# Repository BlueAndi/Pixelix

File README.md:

# PIXELIX <!-- omit in toc -->

Full RGB LED matrix, based on an ESP32 and WS2812B LEDs.

Click on the preview to see the video.

\

___

## Table of Content <!-- omit in toc -->

- [Motivation](#motivation)
- [Introduction](#introduction)
- [Features](#features)
- [Original Setup](#original-setup)
- [Attention](#attention)
- [Supported Development Boards](#supported-development-boards)
  - [Recommendation](#recommendation)
  - [Special Variants](#special-variants)
- [Installation](#installation)
  - [Install A Prebuilt Release With The Web USB Installer](#install-a-prebuilt-release-with-the-web-usb-installer)
  - [Install A Prebuilt Release Manually](#install-a-prebuilt-release-manually)
  - [Build And Install The Software Yourself](#build-and-install-the-software-yourself)
  - [Verify The Installation](#verify-the-installation)
  - [Update A Running PIXELIX](#update-a-running-pixelix)
- [Very First Startup](#very-first-startup)
  - [Variant 1: Configure WiFi station SSID and passphrase using a browser](#variant-1-configure-wifi-station-ssid-and-passphrase-using-a-browser)
  - [Variant 2: Configure WiFi station SSID and passphrase using a serial terminal](#variant-2-configure-wifi-station-ssid-and-passphrase-using-a-serial-terminal)
  - [PIXELIX Is Ready](#pixelix-is-ready)
- [User Interface](#user-interface)
  - [One button control](#one-button-control)
  - [Two button control (LILYGO® T-Display ESP32-S3)](#two-button-control-lilygo-t-display-esp32-s3)
  - [Three button control (Ulanzi TC001)](#three-button-control-ulanzi-tc001)
  - [Remote button](#remote-button)
- [Details](#details)
- [FAQ](#faq)
  - [Where to change panel topology of the LED matrix?](#where-to-change-panel-topology-of-the-led-matrix)
  - [How to change text properties?](#how-to-change-text-properties)
  - [The display only shows an error code, like "E4". What does that mean?](#the-display-only-shows-an-error-code-like-e4-what-does-that-mean)
  - [How can I use animated icons?](#how-can-i-use-animated-icons)
  - [How do I know that my sensor is recognized?](#how-do-i-know-that-my-sensor-is-recognized)
  - [Why do I see sometimes values from the LDR in the SensorPlugin, although no LDR is installed?](#why-do-i-see-sometimes-values-from-the-ldr-in-the-sensorplugin-although-no-ldr-is-installed)
  - [How can I use alternative icons?](#how-can-i-use-alternative-icons)
  - [Is it possible to use a font with 8px height?](#is-it-possible-to-use-a-font-with-8px-height)
  - [How to configure the date/time format?](#how-to-configure-the-datetime-format)
  - [How to configure my own list of plugins?](#how-to-configure-my-own-list-of-plugins)
  - [Is there an easy way to rotate the display by 180° ? I need to turn the display when putting it into a housing](#is-there-an-easy-way-to-rotate-the-display-by-180--i-need-to-turn-the-display-when-putting-it-into-a-housing)
- [Used Libraries](#used-libraries)
- [Issues, Ideas And Bugs](#issues-ideas-and-bugs)
- [License](#license)
- [Contribution](#contribution)

## Motivation

My initial goal was to have a remote display that would show multiple kind of information and run reliably 24/7. Can be connected to the local network via WiFi and controlled via REST API or Websocket. PIXELIX was born!

## Introduction

PIXELIX firmware runs on ESP32 boards and controls RGB LED matrices or TFT displays. It can display the time, date, weather, text, animations, and more.
It requires no cloud connection or smart home system, but its REST and MQTT APIs integrate with [Home Assistant](https://www.home-assistant.io/) and other smart home systems.

## Features

- Supports 32x8, 32x16 and 64x64 LED matrix size out of the box.
- Supports some small TFT displays to simulate a LED matrix in retro style.
- Display static or scrolling text, as well as static or animated icons (BMP, GIF and additional for boards with PSRAM PNG and WEBP).
- Includes a web interface for configuration and control.
- Supports REST and MQTT API for remote control and integration with other systems, like [Home Assistant](https://www.home-assistant.io/).
- Extendable with custom effects and animations by plugins. See list of [plugins](./doc/PLUGINS.md).
- Its plugin concept allows to scale for different development boards.

Not every feature is available on every development board. For example, MQTT generally requires a board with at least 8 MB of flash, except for the Ulanzi TC001. See the `config<variant>.ini` files in the [config](./config) folder for details.

| Some impressions                                                           |                                                                |
| -------------------------------------------------------------------------- | -------------------------------------------------------------- |
|                 |    |
|  |  |
|        | ...                                                            |

The native environment runs PIXELIX as an application on Windows and Linux without requiring hardware. It displays a simulated LED grid in a window and serves its web interface on local port 8080. Melodies that would play through a board's buzzer use the host's audio device. You can mute them with the _Mute_ entry in the simulator window's menu bar.

## Original Setup

The original setup for development and the first release was:

- [ESP32 DevKitV1](https://github.com/playelek/pinout-doit-32devkitv1)
- WS2812B 5050 8x32 RGB Flexible LED Matrix Panel
- Power supply 5 V / 4 A

The following diagram shows the minimum wiring setup, for example, for the ESP32 DevKit V1. Wiring may differ depending on your development board.

## Attention

> :warning: **If you power the development board and LED matrix via USB**, be careful: excessive LED current can damage the ESP32 board. Avoid increasing the display brightness or filling it completely with white pixels. Use an external power supply rated for at least 5 V / 4 A.

> :information_source: To protect your hardware and your eyes, PIXELIX starts at a low brightness. The maximum current is also limited by software.

## Supported Development Boards

In the meantime several other boards are supported as well. You can find them in the [list of boards](./doc/boards/README.md).
If your board is not listed in the main branch, please have a look in the [Development branch](https://github.com/BlueAndi/Pixelix/tree/Development) too.

With the [Ulanzi TC001 smart pixel clock](https://www.ulanzi.com/products/ulanzi-pixel-smart-clock-2882) you even don't need to assemble the electronic and mechanic together.

### Recommendation

If you assemble your own Pixelix hardware, its recommended to use a development board with the following properties:

- 8 MB flash or more. 4 MB flash modules are still supported, but the functionality is limited.
- A esp32 dual core variant, which provides more processing power.
- PSRAM for image formats that require more memory than the available internal RAM, depending on the enabled features.

### Special Variants

Additional supported variants, which were original not in focus:

- [LILYGO&reg; TTGO T-Display ESP32 WiFi and Bluetooth Module Development Board For Arduino 1.14 Inch LCD](http://www.lilygo.cn/prod_view.aspx?TypeId=50033&Id=1126&FId=t3:50033:3)
- [LILYGO&reg; T-Display ESP32-S3 1.9 inch ST7789 LCD Display Touch Screen Development Board](https://www.lilygo.cc/products/t-display-s3)
- Limited HUB75 panel support, configured for the ESP32-DoIt DevKit v1 and the Adafruit MatrixPortal S3 development board.

Although PIXELIX was designed to show information, that is pushed or pulled via REST API, the following sensors can be directly connected and evaluated:

- Temperature and humidity sensors DHTx
- Temperature and humidity sensors SHT3x
- Digitial microphone INMP441 for some sound reactive stuff.

## Installation

PIXELIX can be installed in two different ways. Decide first which one applies to you, because it determines whether you need a build toolchain at all.

| Your situation                                                                                                                                                                                                                 | Way to go                                                                                                                                                                                                                                    |
| ------------------------------------------------------------------------------------------------------------------------------------------------------------------------------------------------------------------------------ | -------------------------------------------------------------------------------------------------------------------------------------------------------------------------------------------------------------------------------------------- |
| You use one of the [supported development boards](#supported-development-boards) with its standard display and the panel wiring matches.                                                                                       | Install a prebuilt release. No toolchain required, nothing needs to be compiled. Use the [web USB installer](#install-a-prebuilt-release-with-the-web-usb-installer) or [flash the binaries manually](#install-a-prebuilt-release-manually). |
| Your board/display combination is not released, your LED matrix size or panel topology is different, you want another set of plugins, you want to rotate the display by 180&deg; or you want to develop a plugin or fix a bug. | [Build and install the software yourself](#build-and-install-the-software-yourself).                                                                                                                                                         |

Every release provides ready-to-flash binaries for all supported board and display combinations. They are named after their build environment, e.g. ```esp32doit-devkit-v1-LED-32x8```, which encodes the development board as well as the display type and its resolution.

> :warning: A prebuilt binary has the LED matrix width/height, the panel topology and the list of plugins compiled in. None of them can be changed later in the web interface. If one of them does not match your hardware, you have to build the software yourself.

### Install A Prebuilt Release With The Web USB Installer

This is the easiest way and the recommended one for everybody who does not want to touch the source code. The installer runs completely in the browser, writes a full flash image (bootloader, partition table, factory image, firmware and filesystem) and can hand over the WiFi credentials over USB afterwards.

1. Open the [PIXELIX USB installer](https://blueandi.github.io/Pixelix/) in a Chromium based desktop browser, like Chrome, Edge, Opera or Brave. It is based on the Web Serial API, which is not available in Firefox, Safari or on mobile devices.
2. Choose the version. The latest stable release is preselected. All releases from version 11 on are offered; pre-releases are marked as such and are not recommended for productive use.
3. Choose your board and display configuration.
4. Connect the development board to your PC with a data capable USB cable and select the serial device once.
5. Start _Erase and install_. Note, that the flash is erased completely, which includes all settings of a previous installation.
    - To keep the settings of a previous installation, enable _Keep settings_ before. The flash is then not erased and the device settings stored in NVS survive: WiFi credentials, hostname, web login, brightness, timezone and so on. The slot configuration, MQTT, sensor calibration, timers and the plugin configuration are reset in any case, because they are part of the filesystem which is always written. Don't use it for the first installation on a board.
6. Keep the USB cable connected and continue with the WiFi setup on the same page. If that succeeds, you can skip the [Very First Startup](#very-first-startup).

If the board does not enter the download mode automatically, follow the BOOT/RESET sequence shown on the page. This is typically necessary for the ESP32 DevKit V1.

### Install A Prebuilt Release Manually

Use this way if no Chromium based browser is available or if you prefer the classic Espressif tools.

1. Download the binaries from the [latest release](https://github.com/BlueAndi/Pixelix/releases).
2. Write them to the flash with the Espressif Flash Download Tool (Windows only) or with esptool (any OS). The detailed steps, the required flash addresses and the flash layout are documented in [Upload/Update the software and the filesystem](./doc/config/SW-UPDATE.md).
3. Continue with the [Very First Startup](#very-first-startup).

See the [software update guide](./doc/config/SW-UPDATE.md#native-application) for native release downloads and installation.

### Build And Install The Software Yourself

> :information_source: The order matters. Configure the display **before** the first build, because the display configuration is compiled into the firmware.

1. Setup the [toolchain](./doc/config/TOOLCHAIN-INSTALLATION.md).
2. Configure your display in ```./config/display.ini```:
   - Adapt _CONFIG_LED_MATRIX_WIDTH_ and _CONFIG_LED_MATRIX_HEIGHT_ according to your LED matrix.
   - Change _CONFIG_LED_TOPO_ according to your physical panel topology. Take a look how your pixels are wired on the pcb and use the following page to choose the right one: [https://github.com/Makuna/NeoPixelBus/wiki/Layout-objects](https://github.com/Makuna/NeoPixelBus/wiki/Layout-objects)
   - Optional: set _CONFIG_DISPLAY_ROTATE180_ to 1 to [rotate the display by 180&deg;](#is-there-an-easy-way-to-rotate-the-display-by-180--i-need-to-turn-the-display-when-putting-it-into-a-housing).
3. Optional: adapt the [list of plugins](#how-to-configure-my-own-list-of-plugins) in the corresponding ```./config/config*.ini```.
4. [Build the software](./doc/config/SW-BUILD.md) and check whether the toolchain works.
5. [Upload the software and the filesystem](./doc/config/SW-UPDATE.md) to the target. Note, that both parts are necessary, the firmware and the filesystem image.
6. Continue with the [Very First Startup](#very-first-startup).

### Verify The Installation

Independent of the way you installed PIXELIX, verify that the LED panel topology is correct and that you see the "Hello World" on the display. If the text is mirrored, scrambled or spread over the wrong rows, the panel topology does not match and the software has to be built with the right _CONFIG_LED_TOPO_ setting.

### Update A Running PIXELIX

Once PIXELIX runs and its web interface is accessible, the firmware and the filesystem can be updated over WiFi with the PIXELIX Updater: [https://github.com/BlueAndi/PixelixUpdater](https://github.com/BlueAndi/PixelixUpdater). You can access the Updater through the submenu "Update" of PIXELIX's web interface. Reinstalling via USB is not necessary for an update.

## Very First Startup

When the device starts for the very first time, the WiFi station SSID and passphrase settings are empty. They can be configured in two possible ways:

1. Using the browser and set them in the captive portal.
2. Using a serial terminal connecting via USB.

### Variant 1: Configure WiFi station SSID and passphrase using a browser

As long as no WiFi station SSID and passphrase are configured, PIXELIX spawns a WiFi access point automatically on every startup. Just wait until it shows the SSID of the access point, search for it with your mobile device and connect.

Once the WiFi station SSID and passphrase are configured, PIXELIX connects to your WiFi network instead. To get back into the access point mode on purpose - e.g. after you replaced your router - restart the device and **keep the button pressed** until the access point SSID is shown.

- SSID: **pixelix-&lt;DEVICE-ID&gt;**
- Passphrase: **Luke, I am your father.**

Depending on your device, you may see a notification prompting you to open the captive portal. Otherwise, enter `http://192.169.4.1` in your browser's address bar.

Use the following default credentials to get access to the PIXELIX web interface:

- User: **luke**
- Password: **skywalker**

### Variant 2: Configure WiFi station SSID and passphrase using a serial terminal

Connect PIXELIX to your PC via USB and start a serial terminal. Use the following commands to set the WiFi SSID and passphrase of your home WiFi network:

- Write WiFi passphrase: ```write wifi passphrase <your-passphrase>```
- Write WiFi SSID: ```write wifi ssid <your-ssid>```
- Restart PIXELIX: ```restart```
- Get IP-address: ```get ip```
- Get hostname: ```get hostname```
- Get status: ```get status```
  - A status of 0 means everything is ok.
  - For any other status, see the [low-level error code table](#the-display-only-shows-a-error-code-like-e4-what-does-that-mean). For example, status 1 corresponds to error code E1.

Use ```help``` to get a list of all supported commands.

### PIXELIX Is Ready

After configuration, restart PIXELIX. It will then be available on your Wi-Fi network.

To change what is displayed, open the web interface and use the same credentials as for the captive portal in Variant 1. On the **Display** page, configure it to suit your needs.

## User Interface

Pixelix can be controlled with buttons. Most of the development boards are supported with just one user button.

### One button control

- 1 short pulse: Activates the next slot.
- 2 short pulses: Activates the previous slot.
- 3 short pulses: Activates next fade effect.
- 4 short pulses: IP address is shown.
- 5 short pulses: Toggle display power on/off.
- Long pressed: Increases the display brightness until maximum and then decreases until minimum. After that it will again increases it and so on.

### Two button control (LILYGO&reg; T-Display ESP32-S3)

- Left button:
  - 1 short pulses: Activates the previous slot.
  - 2 short pulses: Toggle display power on/off.
  - Long pressed: Decreases the display brightness until minimum.
- Right button
  - 1 short pulse: Activates the next slot.
  - 2 short pulses: Activates next fade effect.
  - 3 short pulses: IP address is shown.
  - Long pressed: Increases the display brightness until maximum.

### Three button control (Ulanzi TC001)

- Left button:
  - 1 short pulses: Activates the previous slot.
  - Long pressed: Decreases the display brightness until minimum.
- Ok button:
  - 1 short pulses: Activates next fade effect.
  - 2 short pulses: IP address is shown.
  - Long pressed: Toggle display power on/off.
- Right button
  - 1 short pulse: Activates the next slot.
  - Long pressed: Increases the display brightness until maximum.

### Remote button

If the display's location is hard to reach, the remote user button feature can be used. It is controllable via REST API and perfect for remote buttons like the [Shelly Button 1](https://shelly.cloud/products/shelly-button-1-smart-home-automation-device/).

## Details

- [Home Assistant](./doc/HOMEASSISTANT.md)
- [REST API](https://app.swaggerhub.com/apis/BlueAndi/Pixelix/1.10.0)
- [MQTT API](./doc/MQTT.md)
- More information is in the [documentation](./doc/README.md) folder.

## FAQ

### Where to change panel topology of the LED matrix?

Adapt in ```./config/display.ini``` the _CONFIG_LED_MATRIX_WIDTH_ and _CONFIG_LED_MATRIX_HEIGHT_ according your LED matrix and change _CONFIG_LED_TOPO_ according to your physical panel topology. Take a look how your pixels are wired on the pcb and use the following page to choose the right one: [https://github.com/Makuna/NeoPixelBus/wiki/Layout-objects](https://github.com/Makuna/NeoPixelBus/wiki/Layout-objects)

### How to change text properties?

Text properties can be changed using different keywords added to the string to be displayed.
In order to be able to use these keywords, they must be inside curly braces, otherwise they will only be treated as text.

The following keywords are available:

| Keyword                               | Description                                                                              |
| ------------------------------------- | ---------------------------------------------------------------------------------------- |
| `{#RRGGBB}`                           | Set solid text color (`RRGGBB` in hex)                                                   |
| `{lgv #RRGGBB,#RRGGBB,OFFSET,LENGTH}` | Set linear vertical gradient text color (`RRGGBB` in hex, `OFFSET`/`LENGTH` in pixels)   |
| `{lgh #RRGGBB,#RRGGBB,OFFSET,LENGTH}` | Set linear horizontal gradient text color (`RRGGBB` in hex, `OFFSET`/`LENGTH` in pixels) |
| `{stc}`                               | Activate solid text color                                                                |
| `{lgtc}`                              | Activate linear gradient text color                                                      |
| `{hl}`                                | Horizontal alignment left                                                                |
| `{hc}`                                | Horizontal alignment right                                                               |
| `{hr}`                                | Horizontal alignment center                                                              |
| `{vt}`                                | Vertical alignment top                                                                   |
| `{vc}`                                | Vertical alignment center                                                                |
| `{vb}`                                | Vertical alignment bottom                                                                |
| `{0xCC}`                              | Special character code (CC in hex)                                                       |

**Notes**:

- If these keywords are used via the [REST API](https://app.swaggerhub.com/apis/BlueAndi/Pixelix/1.10.0) all unsafe ASCII characters must be replaced by the respective percent encoding (see also [ASCII Encoding Reference](https://www.w3schools.com/tags/ref_urlencode.ASP)).
- The keywords can be combined.
- Don't add additional spaces, e.g. after a comma. Write them exactly as the format is specified.

**Examples**:

| Sourcecode         | URL                 | Result                                                                             |
| ------------------ | ------------------- | ---------------------------------------------------------------------------------- |
| `{hl}{#ff0000}Hi!` | `%7Bcl%7Dff0000Hi!` | <span style="color:red">Hi!</span>&nbsp;&nbsp;&nbsp;&nbsp;&nbsp;&nbsp;&nbsp;&nbsp; |
| `{hc}{#ff0000}Hi!` | `%7Bhc%7Dff0000Hi!` | &nbsp;&nbsp;&nbsp;&nbsp;<span style="color:red">Hi!</span>&nbsp;&nbsp;&nbsp;&nbsp; |
| `{hr}{#ff0000}Hi!` | `%7Bhr%7Dff0000Hi!` | &nbsp;&nbsp;&nbsp;&nbsp;&nbsp;&nbsp;&nbsp;&nbsp;<span style="color:red">Hi!</span> |

### The display only shows an error code, like "E4". What does that mean?

This is a low level error code. Please have a look into the following table.

| Error code | Description                                                                            |
| ---------- | -------------------------------------------------------------------------------------- |
| E1         | Something happened, which can not be further explained, but was fatal.                 |
| E2         | There is a problem with the two-wire (i2c) interface.                                  |
| E3         | There is no user button available.                                                     |
| E4         | Bad filesystem, did you explicit program the filesystem too? If not, please upload it. |
| E5         | The display manager didn't start up.                                                   |
| E6         | The system message handler didn't start up.                                            |
| E7         | One of the services failed to start.                                                   |

Press a button and Pixelix will jump to the Pixelix Updater.

### How can I use animated icons?

Use animated GIF images to get animated icons. The sprite sheet support (< v8.0.0) was replaced with the GIF images.

If you like to create animated GIFs by yourself, the [Piskel](https://www.piskelapp.com/) editor is recommended. Piskel is a free online editor for animated sprites & pixel art.

### How do I know that my sensor is recognized?

1. Check the log output from USB (not via web interface) right after startup (at this point WiFi is not connected yet).
2. Install the SensorPlugin and open the SensorPlugin website. There the sensor should be shown in the drop-down.

### Why do I see sometimes values from the LDR in the SensorPlugin, although no LDR is installed?

The LDR pin is configured as input (ADC) and it seems that the pin is floating, because there is the ext. pull-down missing.

### How can I use alternative icons?

Find details in the [icon page](./doc/ICONS.md).

### Is it possible to use a font with 8px height?

There are three font types defined:

- default (6px height)
- normal (6px height)
- large (8px height)

Note, the default font type is "normal".

The font type can be selected per plugin instance in the display web page.

Not all plugin may support this in case they get conflicts with their layout.
If a plugin don't support it, it will use the default font type.

### How to configure the date/time format?

The date/time format used by plugins, e.g. the DateTimePlugin or the SunrisePlugin, can be configured in their configuration JSON file. Use the file editor in the web interface to modify it according to your needs. The file can be found in the ```/configuration``` folder and the filename is ```<PLUGIN-UID>.json```. The format specifiers following [strftime()](https://cplusplus.com/reference/ctime/strftime/).

Examples:

- `%I:%M %p`: 02:30 PM
- `%H:%M`: 14:30
- `%m/%d`: 11/12
- `%d.%m.`: 11.12.
- `%d - %b`: 11 - Nov

You can colorize it by using the [text properties](#how-to-change-text-properties).

### How to configure my own list of plugins?

The available plugins depend on your development board. Boards with only 4 MB of flash cannot fit every plugin, and single-core boards such as the ESP32-S2 may not have enough processing power for some plugins.

Several `.ini` files in the `./config` folder define plugin sets:

- configSmall.ini: Used for boards with 4 MB flash.
- configNormal.ini: Used for boards with 8 MB flash or more.
- configSmallNoI2s.ini: Used for boards with 4 MB flash and less mcu power.

Edit the file used by your board, commenting plugins in or out as needed.

### Is there an easy way to rotate the display by 180° ? I need to turn the display when putting it into a housing

Change option CONFIG_DISPLAY_ROTATE180 in ```config/display.ini``` to 1 as shown below and rebuild.

Example:

```ini
[display:common]
build_flags =
    -D CONFIG_DISPLAY_ROTATE180=1
```

## Used Libraries

| Library                                                                       | Description                                                                                                                                                                                        | License                                       |
| ----------------------------------------------------------------------------- | -------------------------------------------------------------------------------------------------------------------------------------------------------------------------------------------------- | --------------------------------------------- |
| [Arduino](https://github.com/platformio/platform-espressif32)                 | ESP32 Arduino framework v2.x.x                                                                                                                                                                     | Apache-2.0                                    |
| [PlatformIO](https://platformio.org)                                          | PlatformIO is a cross-platform, cross-architecture, multiple framework, professional tool for embedded systems engineers and for software developers who write applications for embedded products. | Apache-2.0                                    |
| [NeoPixelBus](https://github.com/Makuna/NeoPixelBus)                          | Controlling the LED matrix with hardware support (I2S)                                                                                                                                             | LGPL-3.0                                      |
| [ESPAsyncWebServer](https://github.com/ESP32Async/ESPAsyncWebServer)          | Webserver                                                                                                                                                                                          | LGPL-3.0                                      |
| [AsyncTCP](https://github.com/ESP32Async/AsyncTCP)                            | This is a fully asynchronous TCP library, aimed at enabling trouble-free, multi-connection network environment for Espressif's ESP32 MCUs.                                                         | LGPL-3.0                                      |
| [ArduinoJson](https://arduinojson.org/)                                       | JSON handling                                                                                                                                                                                      | MIT                                           |
| [StreamUtils](https://github.com/bblanchon/ArduinoStreamUtils)                | Stream utilities                                                                                                                                                                                   | MIT                                           |
| [Bootstrap](https://getbootstrap.com/)                                        | CSS Framework                                                                                                                                                                                      | MIT                                           |
| [POPPER JS](https://popper.js.org/)                                           | POPPER JS                                                                                                                                                                                          | MIT                                           |
| [Adafruit Unified Sensor Driver](https://github.com/adafruit/Adafruit_Sensor) | A unified sensor abstraction layer.                                                                                                                                                                | Apache License 2.0                            |
| [Adafruit DHT sensor library](https://github.com/adafruit/DHT-sensor-library) | An Arduino library for the DHT series of low-cost temperature/humidity sensors.                                                                                                                    | MIT                                           |
| [arduino-sht](https://github.com/Sensirion/arduino-sht)                       | An Arduino library for reading the SHT3x family of temperature and humidity sensors.                                                                                                               | BSD-3-Clause                                  |
| [TFT_eSPI](https://github.com/Bodmer/TFT_eSPI)                                | Arduino and PlatformIO IDE compatible TFT library optimised for the Raspberry Pi Pico (RP2040), STM32, ESP8266 and ESP32 that supports different driver chips                                      | Mixed licenses: MIT, BSD, FreeBSD             |
| [arduinoFFT](https://github.com/kosme/arduinoFFT)                             | Fast Fourier Transform for Arduino.                                                                                                                                                                | GPL 3.0                                       |
| [mufonts](https://github.com/muwerk/mufonts)                                  | A collection of fonts compatible with Adafruit GFX library. These fonts were developed when creating various samples for mupplet display code.                                                     | MIT                                           |
| [JSZip](https://github.com/Stuk/jszip)                                        | A library for creating, reading and editing .zip files with JavaScript, with a lovely and simple API.                                                                                              | MIT                                           |
| [FileSaver.js](https://github.com/eligrey/FileSaver.js)                       | FileSaver.js is the solution to saving files on the client-side.                                                                                                                                   | MIT                                           |
| [Arduino client for MQTT](https://github.com/knolleary/pubsubclient)          | This library provides a client for doing simple publish/subscribe messaging with a server that supports MQTT.                                                                                      | MIT                                           |
| [ESP32-PSRamFS](https://github.com/tobozo/ESP32-PsRamFS)                      | ESP32-PsRamFS is a pseudo RamDisk library for Arduino-ESP32, with vfs compliance.                                                                                                                  | MIT                                           |
| [Dear ImGui](https://github.com/ocornut/imgui)                                | ImGui is a bloat-free graphical user interface library for C++. Is is used by the native Platfrom only to create a simulated LED grid window.                                                      | MIT                                           |
| [PNGdec](https://github.com/bitbank2/PNGdec)                                  | PNG image decoding. Only built for boards with PSRAM.                                                                                                                                              | Apache-2.0                                    |
| [libwebp](https://github.com/webmproject/libwebp)                             | WebP image decoding (static and animated), vendored decoder-only. Only built for boards with PSRAM.                                                                                                | BSD-3-Clause, plus an additional patent grant |

## Issues, Ideas And Bugs

If you have ideas or found a bug, create an [issue](https://github.com/BlueAndi/Pixelix/issues). If you want to fix it yourself, clone the repository and open a pull request. For questions to the community or showing the own Pixelix, the [Discord server](https://discord.gg/D3uYhBQBhf) can be used.

## License

The whole source code is published under the [MIT license](http://choosealicense.com/licenses/mit/).
Consider the different licenses of the used third party libraries too!

## Contribution

Unless you explicitly state otherwise, any contribution intentionally submitted for inclusion in the work by you, shall be licensed as above, without any
additional terms or conditions.

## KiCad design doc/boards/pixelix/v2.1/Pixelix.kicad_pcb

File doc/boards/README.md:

# PIXELIX <!-- omit in toc -->

## Boards <!-- omit in toc -->

Pixelix supports different ESP32 development boards. Own PCBs were developed too for easier assembling of e.g. the LED matrix, sensors, etc.

To find out which part shall be connected to which pin of your development board you can see in the following chapters.

- [Development Boards](#development-boards)
  - [Overview](#overview)
  - [Adafruit ESP32 Feather V2](#adafruit-esp32-feather-v2)
  - [Adafruit MatrixPortal ESP32-S3 - HUB75 panel](#adafruit-matrixportal-esp32-s3---hub75-panel)
  - [AZ-Delivery ESP-32 Dev Kit C V4](#az-delivery-esp-32-dev-kit-c-v4)
  - [DOIT ESP32 DEVKIT V1](#doit-esp32-devkit-v1)
  - [DOIT ESP32 DEVKIT V1 - HUB75 panel](#doit-esp32-devkit-v1---hub75-panel)
  - [ESP32-S3 DEVKITC-1-N16R8V](#esp32-s3-devkitc-1-n16r8v)
  - [ESP32 NodeMCU](#esp32-nodemcu)
  - [LILYGO® TTGO ESP32 T-Display](#lilygo-ttgo-esp32-t-display)
  - [LILYGO® ESP32 T-Display S3](#lilygo-esp32-t-display-s3)
  - [M5Stack Core ESP32 WiFi and Bluetooth Module Development Board](#m5stack-core-esp32-wifi-and-bluetooth-module-development-board)
  - [WEMOS Lolin S2 Mini](#wemos-lolin-s2-mini)
- [Pixelix Board v1.5](#pixelix-board-v15)
- [Pixelix Board v2.0](#pixelix-board-v20)
- [Pixelix Board v2.1](#pixelix-board-v21)
- [Ulanzi TC001 smart pixel clock](#ulanzi-tc001-smart-pixel-clock)
- [Issues, Ideas And Bugs](#issues-ideas-and-bugs)
- [License](#license)
- [Contribution](#contribution)

## Development Boards

### Overview

| Eval. Board                      | MCU      | Cores | Frequency | SRAM (DRAM/IRAM) | PSRAM | Flash      |
| -------------------------------- | -------- | ----- | --------- | ---------------- | ----- | ---------- |
| Adafruit ESP32 Feather V2        | ESP32    | 2     | 240 MHz   | 520 kB (320/200) | 2 MB  | 8 MB       |
| Adafruit MatrixPortal ESP32-S3   | ESP32-S3 | 2     | 240 MHz   | 520 kB (320/200) | 2 MB  | 8 MB       |
| AZ-Delivery ESP-32 Dev Kit C V4  | ESP32    | 2     | 240 MHz   | 520 kB (320/200) | -     | 4 MB       |
| DOIT ESP32 DEVKIT V1             | ESP32    | 2     | 240 MHz   | 520 kB (320/200) | -     | 4 MB       |
| ESP32-S3 DEVKITC-1-N16R8V        | ESP32-S3 | 2     | 240 MHz   | 520 kB (320/200) | 8 MB  | 16 MB      |
| ESP32 NodeMCU                    | ESP32    | 2     | 240 MHz   | 520 kB (320/200) | -     | 4 MB       |
| LILYGO&reg; TTGO ESP32 T-Display | ESP32    | 2     | 240 MHz   | 520 kB (320/200) | -     | 4 or 16 MB |
| LILYGO&reg; ESP32 T-Display S3   | ESP32-S3 | 2     | 240 MHz   | 520 kB (320/200) | 8 MB  | 16 MB      |
| M5Stack Core ESP32               | ESP32    | 2     | 240 MHz   | 520 kB (320/200) | -     | 16 MB      |
| WEMOS Lolin S2 Mini              | ESP32-S2 | 1     | 240 MHz   | 520 kB (320/200) | 2 MB  | 4 MB       |
| Ulanzi TC001                     | ESP32    | 2     | 240 MHz   | 520 kB (320/200) | -     | 4 MB       |

### Adafruit ESP32 Feather V2

- Manufacturer: [Adafruit](https://learn.adafruit.com/adafruit-esp32-feather-v2)
- Pinning:
  - Board: [board:adafruit_feather_esp32_v2-LED-32x8](../../config/board.ini)
  - Display: [display:led_matrix_column_major_alternating](../../config/display.ini)
- Compatible with Pixelix boards.

### Adafruit MatrixPortal ESP32-S3 - HUB75 panel

- Manufacturer: [Adafruit](https://learn.adafruit.com/adafruit-matrixportal-s3)
- Pinning:
  - Board: [board:adafruit_matrixportal_s3-HUB75-64x64](../../config/board.ini)
  - Display: [display:hub75-adafruit-matrixportal-esp32s3](../../config/display.ini)
- Not compatible with Pixelix boards.
- [Housing](./hub75/housing/hub75.scad) for HUB74 64x64 pixel 3 mm pitch (192x192x15 mm)

### AZ-Delivery ESP-32 Dev Kit C V4

- Manufacturer: [AZ-Delivery](https://www.az-delivery.de/products/esp-32-dev-kit-c-v4)
- Pinning:
  - Board: [board:az-delivery-devkit-v4-LED-32x8](../../config/board.ini)
  - Display: [display:led_matrix_column_major_alternating](../../config/display.ini)
- Compatible with Pixelix boards.

### DOIT ESP32 DEVKIT V1

- Pinning:
  - Board: [board:esp32doit-devkit-v1-LED-32x8](../../config/board.ini)
  - Display: [display:led_matrix_column_major_alternating](../../config/display.ini)
- Compatible with Pixelix boards.

### DOIT ESP32 DEVKIT V1 - HUB75 panel

- Pinning:
  - Board: [board:esp32doit-devkit-v1-HUB75-64x64](../../config/board.ini)
  - Display: [display:hub75-esp32](../../config/display.ini)
- Pixelix boards doesn't support HUB75 panels.

### ESP32-S3 DEVKITC-1-N16R8V

- Reference design: [ESP32-S3-DevKitC-1](https://docs.espressif.com/projects/esp-dev-kits/en/latest/esp32s3/esp32-s3-devkitc-1/index.html)
- Pinning:
  - LED matrix 32x8
    - Board: [board:esp32-s3-devkitc-1-n16r8v-LED-32x8](../../config/board.ini)
    - Display: [display:led_matrix_column_major_alternating](../../config/display.ini)
  - LED matrix 32x16
    - Board: [board:esp32-s3-devkitc-1-n16r8v-LED-32x16](../../config/board.ini)
    - Display: [display:led_matrix_32x16_column_major_alternating](../../config/display.ini)
- Not compatible with Pixelix boards.

### ESP32 NodeMCU

- Pinning:
  - Board: [board:esp32-nodemcu-LED-32x8](../../config/board.ini)
  - Display: [display:led_matrix_column_major_alternating](../../config/display.ini)
- Compatible with Pixelix boards.

### LILYGO&reg; TTGO ESP32 T-Display

The LILYGO&reg; TTGO ESP32 T-Display is handled separately because it uses its onboard display instead of an external LED matrix.

- Manufacturer: [Lilygo](https://lilygo.cc/products/t-display?srsltid=AfmBOoqYRjCX8MV0n_o-94-pFiF6-dUzS7QKkgV3mP2jYdcxx3uaqSSq)
- Pinning:
  - Board: [board:lilygo-ttgo-t-display-TFT-32x8](../../config/board.ini)
  - Display: [display:lilygo_ttgo_tdisplay](../../config/display.ini)
- Not compatible with Pixelix boards.

### LILYGO&reg; ESP32 T-Display S3

The LILYGO&reg; ESP32 T-Display S3 is handled separately because it uses its onboard display instead of an external LED matrix.

- Manufacturer: [Lilygo](https://www.lilygo.cc/products/t-display-s3)
- Pinning:
  - Variant: 32x8
    - Board: [board:lilygo-t-display-s3-TFT-32x8](../../config/board.ini)
    - Display: [display:lilygo_tdisplay-s3-32x8](../../config/display.ini)
  - Variant: 64x16
    - Board: [board:lilygo-t-display-s3-TFT-64x16](../../config/board.ini)
    - Display: [display:lilygo_tdisplay-s3-64x16](../../config/display.ini)
- Not compatible with Pixelix boards.

### M5Stack Core ESP32 WiFi and Bluetooth Module Development Board

- Manufacturer: [M5Stack](https://m5stack.com/)
- Pinning:
  - Board: [board:m5stack_core-TFT-32x8](../../config/board.ini)
  - Display: [display:m5stack_core](../../config/display.ini)
- Not compatible with Pixelix boards.

### WEMOS Lolin S2 Mini

- Manufacturer: [WEMOS](https://www.wemos.cc/en/latest/s2/s2_mini.html)
- Pinning:
  - Board: [board:wemos_lolin_s2_mini-LED-32x8](../../config/board.ini)
  - Display: [display:led_matrix_column_major_alternating](../../config/display.ini)
- Not compatible with Pixelix boards.

## Pixelix Board v1.5

This board was original developed with a ESP32 DevKit V1 development board as piggy bag.

- [Hardware description](./pixelix/v1.5/ELECTRONIC.md)
- [Bill of material](./pixelix/v1.5/BOM.md)
- [Pinning](../../lib/HalLedMatrix/src/Board.h)
- [Schematic](./pixelix/v1.5/schematics/)
- [PCB](./pixelix/v1.5/pcb/)
- [Housing Part 1](https://www.thingiverse.com/thing:2791276)
- [Housing Part 2](https://www.thingiverse.com/thing:3884621)

## Pixelix Board v2.0

The Pixelix board v2.0 is the successor of Pixelix board v1.5. It was designed for ESP32 DevKit V4 (4 MB flash) and the Adafruit ESP32 Feather V2 (8 MB flash) development board as piggy bag.

- [Hardware description](./pixelix/v2.0/ELECTRONIC.md)
- [Bill of material](./pixelix/v2.0/BOM.md)
- [Pinning](../../lib/HalLedMatrix/src/Board.h)
- [Housing](./pixelix/housing/)

## Pixelix Board v2.1

The Pixelix board v2.1 is the successor of Pixelix board v2.0. It was designed for ESP32 DevKit V4 (4 MB flash) and the Adafruit ESP32 Feather V2 (8 MB flash) development board as piggy bag.

- [Hardware description](./pixelix/v2.1/ELECTRONIC.md)
- [Bill of material](./pixelix/v2.1/BOM.md)
- [Pinning](../../lib/HalLedMatrix/src/Board.h)
- [Housing](./pixelix/housing/)

## Ulanzi TC001 smart pixel clock

- Manufacturer: [Ulanzi](https://www.ulanzi.com/products/ulanzi-pixel-smart-clock-2882)
- Pinning:
  - Board: [board:ulanzi-tc001-LED-32x8](../../config/board.ini)
  - Display: [display:led_matrix_row_major_alternating](../../config/display.ini)

## Issues, Ideas And Bugs

If you have ideas or found a bug, create an [issue](https://github.com/BlueAndi/Pixelix/issues). If you want to fix it yourself, clone the repository and open a pull request.

## License

The whole source code is published under the [MIT license](http://choosealicense.com/licenses/mit/).
Consider the different licenses of the used third party libraries too!

## Contribution

Unless you explicitly state otherwise, any contribution intentionally submitted for inclusion in the work by you, shall be licensed as above, without any
additional terms or conditions.

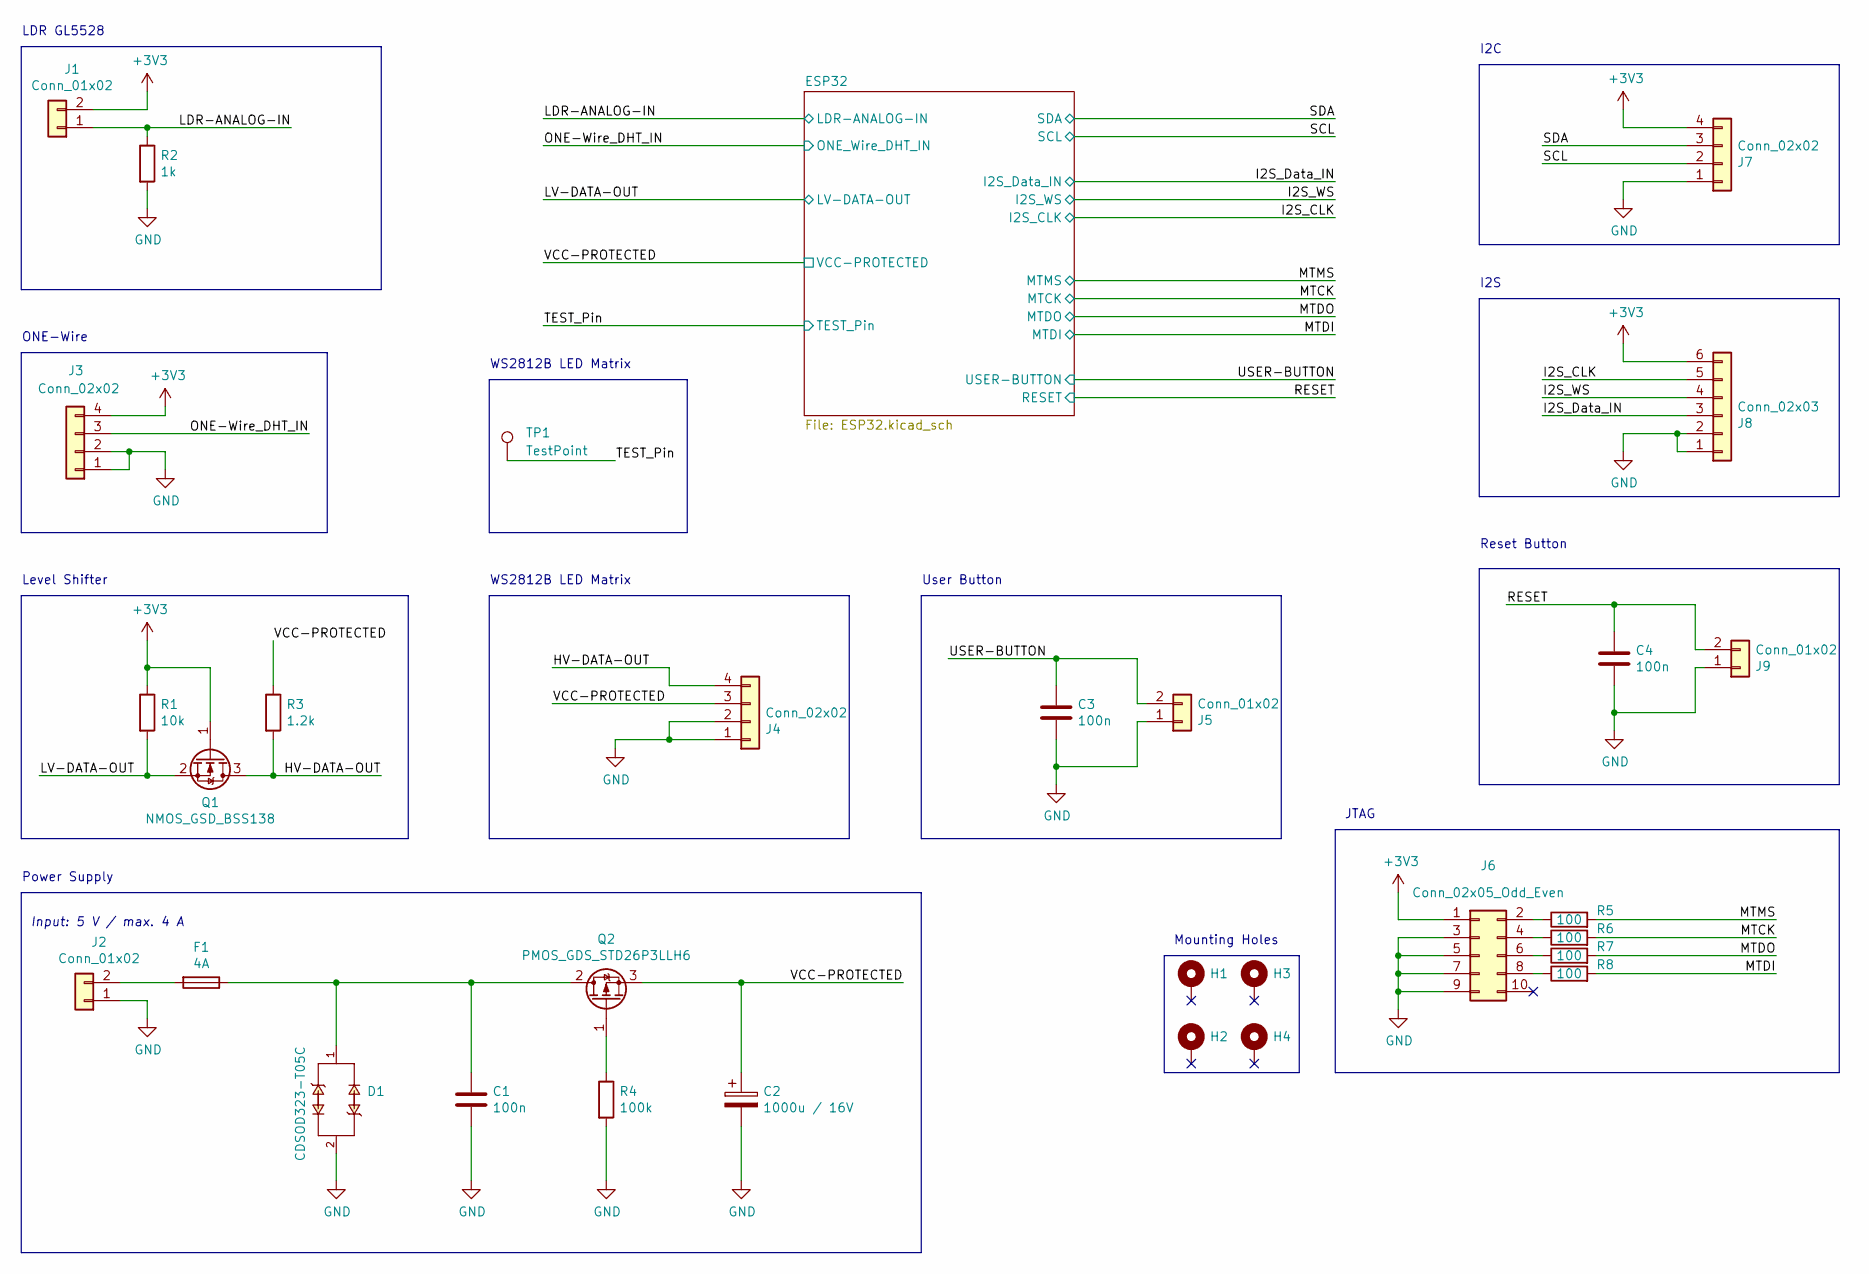
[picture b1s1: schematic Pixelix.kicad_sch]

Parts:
C1, C3, C4: 100n; C_1206_3216Metric_Pad1.33x1.80mm_HandSolder; Part-No. X7R1206B100N
C2: 1000u / 16V; CP_Radial_D8.0mm_P3.50mm_horizontal; Part-No. EEU-FR1C102L
D1: CDSOD323-T05C; Part-No. CDSOD323-T05C
F1: 4A; FUSE_0154004.DR; Part-No. 0154004.DRT
H1, H2, H3, H4: MountingHole_Pad; MountingHole_2.2mm_M2_Pad_Via
J1, J2, J5, J9: Conn_01x02; 66200211022; Part-No. 66200211022
J3, J4, J7: Conn_02x02; 66200421022; Part-No. 66200421022
J6: Conn_02x05_Odd_Even; 61201021621; Part-No. 61201021621
J8: Conn_02x03; 66200621022; Part-No. 66200621022
Q1: NMOS_GSD_BSS138; SOT-23_Handsoldering; Part-No. BSS138
Q2: PMOS_GDS_STD26P3LLH6; TO-252-3_TabPin2; Part-No. STD26P3LLH6
R1: 10k; R_1206_3216Metric_Pad1.30x1.75mm_HandSolder; Part-No. RC1206JR-0710KL
R2: 1k; R_1206_3216Metric_Pad1.30x1.75mm_HandSolder; Part-No. RC1206JR-071KL
R3: 1.2k; R_1206_3216Metric_Pad1.30x1.75mm_HandSolder; Part-No. RC1206JR-071K2L
R4: 100k; R_1206_3216Metric_Pad1.30x1.75mm_HandSolder; Part-No. RK73H2BTTD14
R5, R6, R7, R8: 100; R_1206_3216Metric_Pad1.30x1.75mm_HandSolder; Part-No. RC1206JR-07100RL
TP1: TestPoint; PinHeader_1x01_P2.54mm_Vertical

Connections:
+3V3: J1.2, J3.4, J6.1, J7.4, J8.6, Q1.1 (G), R1.1; also elsewhere on the board
/HV-DATA-OUT: J4.4, Q1.3 (D), R3.2
/I2S_CLK: J8.5; also elsewhere on the board
/I2S_Data_IN: J8.3; also elsewhere on the board
/I2S_WS: J8.4; also elsewhere on the board
/LDR-ANALOG-IN: J1.1, R2.1; also elsewhere on the board
/LV-DATA-OUT: Q1.2 (S), R1.2; also elsewhere on the board
/MTCK: R6.2; also elsewhere on the board
/MTDI: R8.2; also elsewhere on the board
/MTDO: R7.2; also elsewhere on the board
/MTMS: R5.2; also elsewhere on the board
/ONE-Wire_DHT_IN: J3.3; also elsewhere on the board
/RESET: C4.1, J9.2; also elsewhere on the board
/SCL: J7.2; also elsewhere on the board
/SDA: J7.3; also elsewhere on the board
/TEST_Pin: TP1.1; also elsewhere on the board
/USER-BUTTON: C3.1, J5.2; also elsewhere on the board
/VCC-PROTECTED: C2.1, J4.3, Q2.3 (S), R3.1; also elsewhere on the board
GND: C1.2, C2.2, C3.2, C4.2, D1.2, J2.1, J3.1, J3.2, J4.1, J4.2, J5.1, J6.3, J6.5, J6.7, J6.9, J7.1, J8.1, J8.2, J9.1, R2.2, R4.2; also elsewhere on the board
unnamed: F1.2, J2.2
unnamed: J6.2, R5.1
unnamed: J6.4, R6.1
unnamed: J6.6, R7.1
unnamed: J6.8, R8.1
unnamed: C1.1, D1.1, F1.1, Q2.2 (D)
unnamed: Q2.1 (G), R4.1

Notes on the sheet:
User Button
LDR GL5528
WS2812B LED Matrix
I2S
ONE-Wire
JTAG
I2C
Power Supply
Mounting Holes
Input: 5 V / max. 4 A
Level Shifter
Reset Button

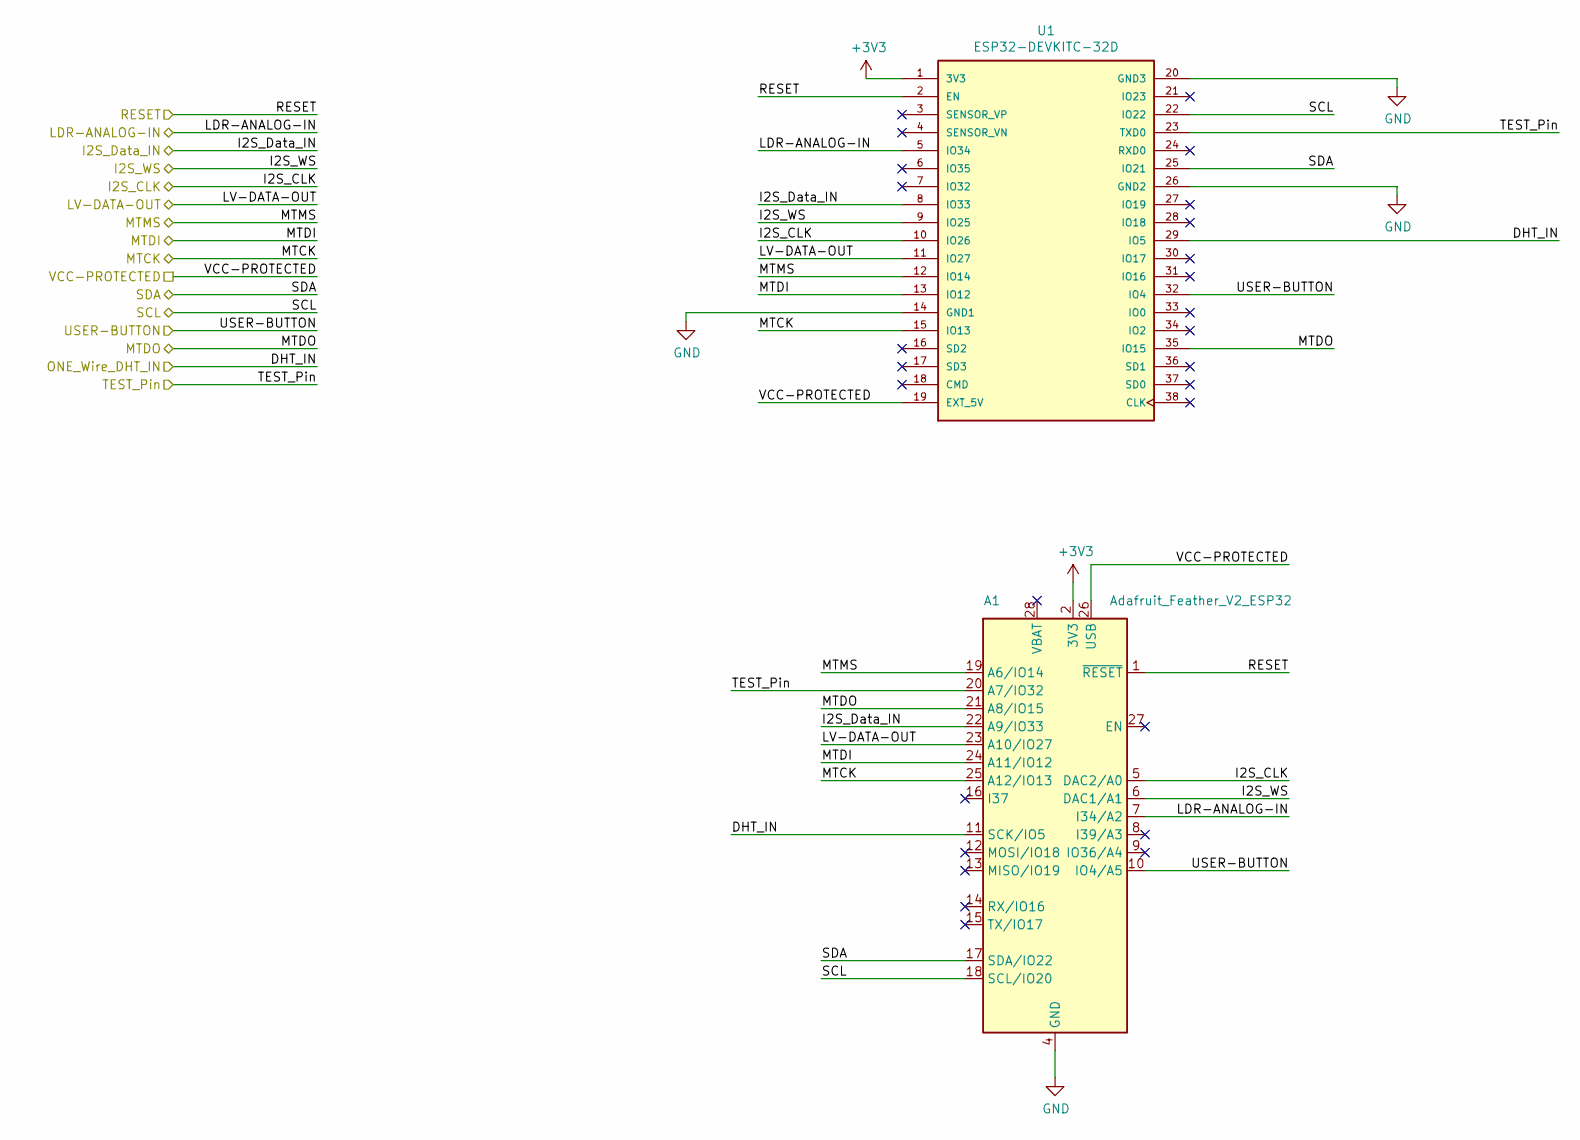
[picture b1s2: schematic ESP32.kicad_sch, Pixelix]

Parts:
A1: Adafruit_Feather_V2_ESP32; Part-No. Feather V2
U1: ESP32-DEVKITC-32D; MODULE_ESP32-DEVKITC-32D; Part-No. ESP32-DEVKITC-32D

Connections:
+3V3: A1.2 (3V3), U1.1 (3V3); also elsewhere on the board
/I2S_CLK: A1.5 (DAC2/A0), U1.10 (IO26); also elsewhere on the board
/I2S_Data_IN: A1.22 (A9/IO33), U1.8 (IO33); also elsewhere on the board
/I2S_WS: A1.6 (DAC1/A1), U1.9 (IO25); also elsewhere on the board
/LDR-ANALOG-IN: A1.7 (I34/A2), U1.5 (IO34); also elsewhere on the board
/LV-DATA-OUT: A1.23 (A10/IO27), U1.11 (IO27); also elsewhere on the board
/MTCK: A1.25 (A12/IO13), U1.15 (IO13); also elsewhere on the board
/MTDI: A1.24 (A11/IO12), U1.13 (IO12); also elsewhere on the board
/MTDO: A1.21 (A8/IO15), U1.35 (IO15); also elsewhere on the board
/MTMS: A1.19 (A6/IO14), U1.12 (IO14); also elsewhere on the board
/ONE-Wire_DHT_IN: A1.11 (SCK/IO5), U1.29 (IO5); also elsewhere on the board
/RESET: A1.1 (~RESET), U1.2 (EN); also elsewhere on the board
/SCL: A1.18 (SCL/IO20), U1.22 (IO22); also elsewhere on the board
/SDA: A1.17 (SDA/IO22), U1.25 (IO21); also elsewhere on the board
/TEST_Pin: A1.20 (A7/IO32), U1.23 (TXD0); also elsewhere on the board
/USER-BUTTON: A1.10 (IO4/A5), U1.32 (IO4); also elsewhere on the board
/VCC-PROTECTED: A1.26 (USB), U1.19 (EXT_5V); also elsewhere on the board
GND: A1.4 (GND), U1.14 (GND1), U1.20 (GND3), U1.26 (GND2); also elsewhere on the board

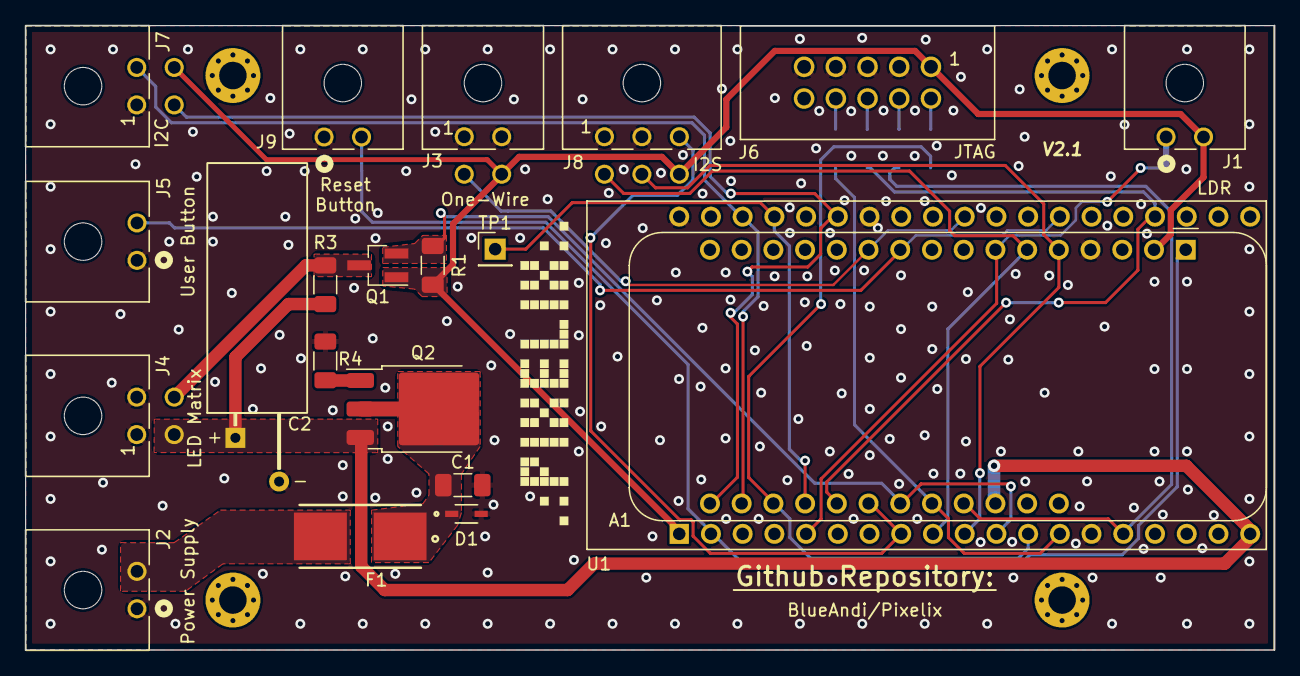
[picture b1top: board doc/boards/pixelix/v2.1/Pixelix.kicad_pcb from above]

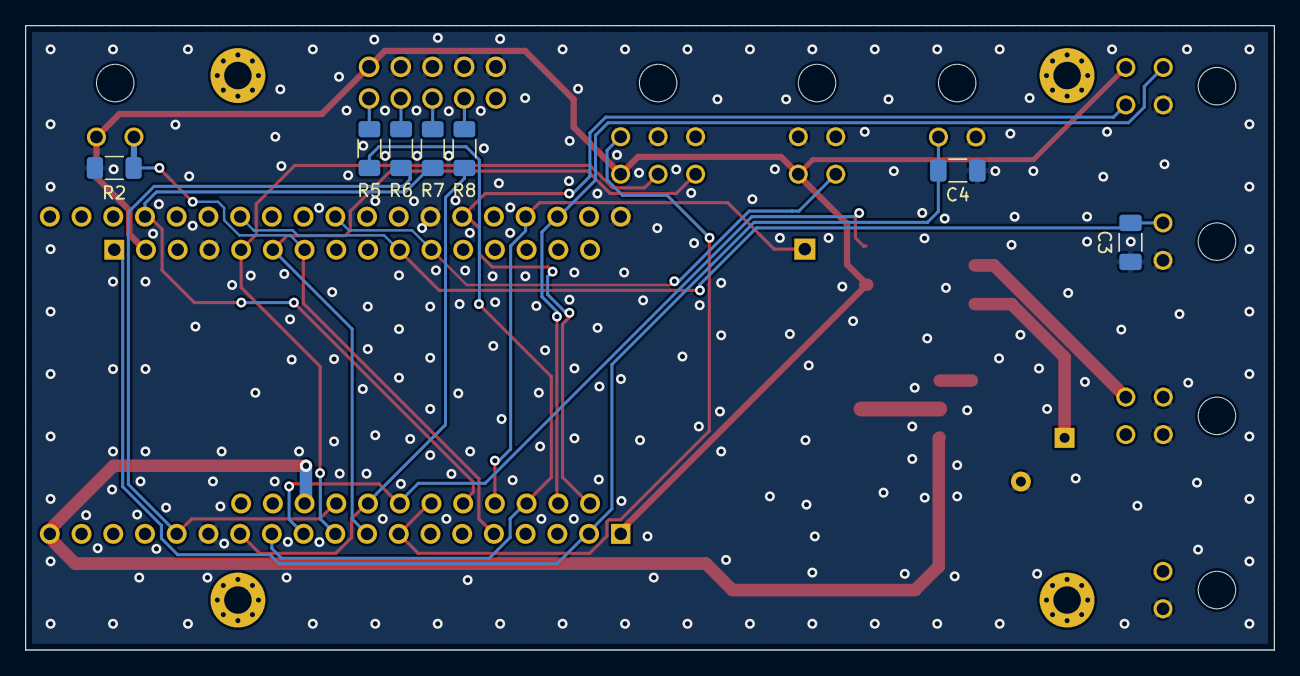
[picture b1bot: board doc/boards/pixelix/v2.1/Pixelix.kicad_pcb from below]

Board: 2 copper layers, 100.0 x 50.0 mm, 32 parts (7 on the bottom side), 26 nets.

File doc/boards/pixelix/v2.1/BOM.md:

# PIXELIX
![PIXELIX](../../../images/LogoBlack.png)

[![License](https://img.shields.io/badge/license-MIT-blue.svg)](http://c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

# BOM

| Amount | Description | Package | Part | URL |
| --- | --- | --- | --- | --- |
| 1 | Adafruit Feather V2 | Feather V2 | A1 | [Adafruit](https://www.adafruit.com/product/5400), [Amazon](https://www.amazon.de/-/en/Adafruit-ESP32-Feather-V2-8MB-Fla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, [Mouser](https://www.mouser.de/ProductDetail/Adafruit/5400?qs=MyNHzdo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 |
| 3 | Capacitor 100 nF | C1206 | C1, C3, C4 | [Reichelt](https://www.reichelt.de/vielschicht-kerko-100nf-50v-125-c-ke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, [Mouser](https://www.mouser.de/ProductDetail/KEMET/C1206C104K5RACTM?q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 |
| 1 | Capacitor 1000 uF / 16 V | E5-8.5 | C2 | [Reichelt](https://www.reichelt.de/elko-radial-1-0-mf-16-v-105-c-low-es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, [Mouser](https://www.mouser.de/ProductDetail/Panasonic/EEU-FR1C102L?q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 |
| 4 | Resistor 100 Ohm | R1206 | R5, R6, R7, R8 | [Reichelt](https://www.reichelt.de/smd-widerstand-1206-100-ohm-250-mw-5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, [Mouser](https://www.mouser.de/ProductDetail/YAGEO/RC1206JR-07100RL?q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 |
| 1 | Resistor 1 kOhm | R1206 | R2 | [Reichelt](https://www.reichelt.de/smd-widerstand-1206-1-0-kohm-250-mw-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, [Mouser](https://www.mouser.de/ProductDetail/YAGEO/RC1206JR-071KL?qs=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  |
| 1 | Resistor 1.2 kOhm | R1206 | R3 | [Reichelt](https://www.reichelt.de/smd-widerstand-1206-1-2-kohm-250-mw-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, [Mouser](https://www.mouser.de/ProductDetail/YAGEO/RC1206JR-071K2L?qs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  |
| 1 | Resistor 10 kOhm | R1206 | R1 | [Reichelt](https://www.reichelt.de/smd-widerstand-1206-10-kohm-250-mw-5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, [Mouser](https://www.mouser.de/ProductDetail/YAGEO/RC1206JR-0710KL?qs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 |
| 1 | Resistor 100 kOhm | R1206 | R4 | [Reichelt](https://www.reichelt.de/smd-widerstand-1206-100-kohm-250-mw-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, [Mouser](https://www.mouser.de/ProductDetail/YAGEO/RC1206FR-07100KL?q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 |
| 1 | ESD suppressor CDSOD323-T05C | SOD-323 | D1 | [Conrad](https://www.conrad.de/de/p/bourns-tvs-diode-cdsod323-t05c-so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, [Farnell](https://de.farnell.com/bourns/cdsod323-t05c/tvs-diode-bidir-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, [Mouser](https://www.mouser.de/ProductDetail/Bourns/CDSOD323-T05C?qs=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 |
| 1 | Micro fuse block, 4A slow | OMNI-BLOK | F1 | [Reichelt](https://www.reichelt.de/smd-sicherungshalter-mit-sicherung-4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, [Farnell](https://de.farnell.com/littelfuse/0154004-drt/sicherung-smd-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, [Mouser](https://www.mouser.de/ProductDetail/?qs=gu7KAQ731UQeedYeniUN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 |
| 1 | Espressif ESP32-DEVKIT | ESP32-DEVKITC-32D | U1 | [Mouser](https://www.mouser.de/ProductDetail/Espressif-Systems/ESP32-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, [Amazon](https://www.amazon.de/s?k=ESP32-DEVKITC-32D&i=computers&__mk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 |
| 1 | N-channel mosfet BSS138 | SOT23 | Q1 | [Reichelt](https://www.reichelt.de/mosfet-n-ch-50v-0-22a-0-36w-sot-23-b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, [Farnell](https://de.farnell.com/on-semiconductor/bss138/mosfet-n-kana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, [Mouser](https://www.mouser.de/ProductDetail/onsemi-Fairchild/BSS138?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 |
| 1 | P-channel mosfet STD26P3LLH6 | TO252 | Q2 | [Reichelt](https://www.reichelt.de/mosfet-p-ch-30v-12a-0-03r-to252-std2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, [Farnell](https://de.farnell.com/stmicroelectronics/std26p3llh6/mosfet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, [Mouser](https://www.mouser.de/ProductDetail/STMicroelectronics/STD26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 |
| 5 | Conn_01x02 | Wuerth Elektronik 66200211022 | J1, J2, J4, J6, J8 | [Farnell](https://de.farnell.com/wurth-elektronik/66200211022/steckv-s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, [Mouser](https://www.mouser.de/c/?q=66200211022) |
| 2 | Conn_01x03 | Wuerth Elektronik 66200311022 | J3, J7 | [Farnell](https://de.farnell.com/wurth-elektronik/66200311022/stiftlei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, [Mouser](https://www.mouser.de/ProductDetail/Wurth-Elektronik/6620031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 |
| 1 | Conn_02x05_Odd_Even | Wuerth Elektronik 61201021621 | J5 | [Farnell](https://de.farnell.com/wurth-elektronik/61201021621/stiftlei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, [Mouser](https://www.mouser.de/ProductDetail/Wurth-Elektronik/6120102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 |
| --- | --- | --- | --- | --- |
| 5 | Plug_01x02 | Wuerth Elektronik 662002013322 | J1*, J2*, J4*, J6*, J8* | [Mouser](https://www.mouser.de/ProductDetail/Wurth-Elektronik/6620020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 |
| 2 | Plug_01x03 | Wuerth Elektronik 662003013322 | J3*, J7* | [Mouser](https://www.mouser.de/ProductDetail/Wurth-Elektronik/6620030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 |
| 1 | WS2812B 5050 8x32 RGB Flexible LED Panel Matrix | - | - | [Amazon](https://www.amazon.de/CHINLY-Flexible-Individuellement-adres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 |
| 1 | Power supply 5 V / 5 A (4 A would be enough) | - | - | [Reichelt](https://www.reichelt.de/tischnetzteil-25-w-5-v-5-a-mw-gst40a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, [Mouser](https://www.mouser.de/ProductDetail/CUI-Inc/SDM36-5-U-P5?qs=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 |
| 1 | Power cable | - | - | [Reichelt](https://www.reichelt.de/netzkabel-schutzkontaktstecker-gew-1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, [Mouser](https://www.mouser.de/ProductDetail/Qualtek/364002-D01?qs=HF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 |
| 1 | Power supply plug | - | - | [Mouser](https://www.mouser.de/ProductDetail/CUI-Devices/PJ-065A?qs=W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 |
| 1 | USER-Button | - | - | [Amazon](https://www.amazon.de/-/en/gp/product/B08L49F7DV) |
| 1 | RESET-Button | - | - | [Amazon](https://www.amazon.de/-/en/gp/product/B08YMZGLWX) |
| 1 | Light Sensor  | LDR5528  | - | [Amazon](https://www.amazon.de/-/en/AZDelivery-pieces-resistor-diodes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 |
| 1 | Audio Sensor-Module | INMP441  | - | [Amazon](https://www.amazon.de/-/en/gp/product/B09JFDJ9BF) |
| 4 | Insert-Nuts M2 | - | - | [Amazon](https://www.amazon.de/ruthex-Gewindeeinsatz-St%C3%BCck-Gewin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

* Note, only **ONE** ESP32 is required. Either U1 or A1.
* Note, you can also use the *Molex 2157601002* connectors for J1, J2, J4, J6 and J8 and the *Molex 2157601003* for J3 and J7.
* Note, you can also use the *Molex 2157591002* plugs for J1*, J2*, J4*, J6* and J8* and the *Molex 2157591003* for J3* and J7*. You also need crimp terminals (e.g. *Wuerth Elektronik 66200113722DEC* or *Molex 2064600021*)
* Do **NOT** combine connectors and plugs from Molex and Wuerth Elektronik!

# Issues, Ideas And Bugs
If you have further ideas or you found some bugs, great! Create a [issue](https://github.com/BlueAndi/Pixelix/issues) or if you are able and willing to fix it by yourself, clone the repository and create a pull request.

# License
The whole source code is published under the [MIT license](http://choosealicense.com/licenses/mit/).

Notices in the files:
doc/boards/pixelix/v2.0/BOM.md:
[License](https://img.shields.io/badge/license-MIT-blue.svg)](http://choosealicense.com/licenses/mit/)
